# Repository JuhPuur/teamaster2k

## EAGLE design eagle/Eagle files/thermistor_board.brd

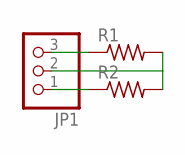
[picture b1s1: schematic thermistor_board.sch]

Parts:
JP1: PINHD-1X3; 1X03
R1, R2: RES-US1206; R1206

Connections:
GND: JP1.1, R2.1
unnamed: JP1.3, R1.1
unnamed: JP1.2, R1.2, R2.2

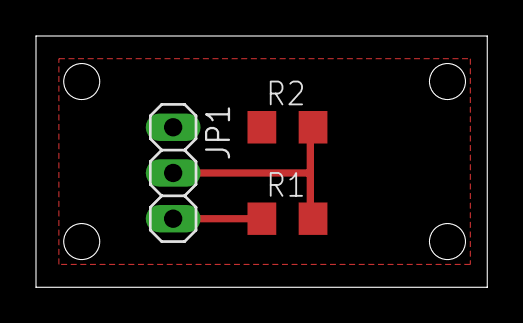
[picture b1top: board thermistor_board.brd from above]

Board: 2 copper layers, 25.1 x 14.0 mm, 3 parts (0 on the bottom side), 3 nets.

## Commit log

2016-03-24 Added readme
2016-03-24 Added files via upload
    All sketches so far.
2016-03-24 Added files via upload
    tea maker and fan sketches
2016-04-03 Added measurements
2016-04-11 PDF files for the lazor
2016-04-11 SVG files for the lazor
2016-04-11 Added cardboard proto photos
    Added cardboard proto photos
2016-04-29 pohjakuvia
2016-04-29 Käyrän siirtoa
2016-05-13 added 3d model for the lid
2016-05-16 fixed the stl model size
2016-05-24 Add files via upload
    kuvat, eagle filut ja kannen stl
2016-05-29 Some photos from the first 3D-prototype
2016-05-29 Photo of the BOM list
2016-06-10 Add files via upload
    Lisäsi kuvia elektroniikasta
2016-06-10 video
2016-06-10 Demo source
2016-06-12 Final images and action shot
